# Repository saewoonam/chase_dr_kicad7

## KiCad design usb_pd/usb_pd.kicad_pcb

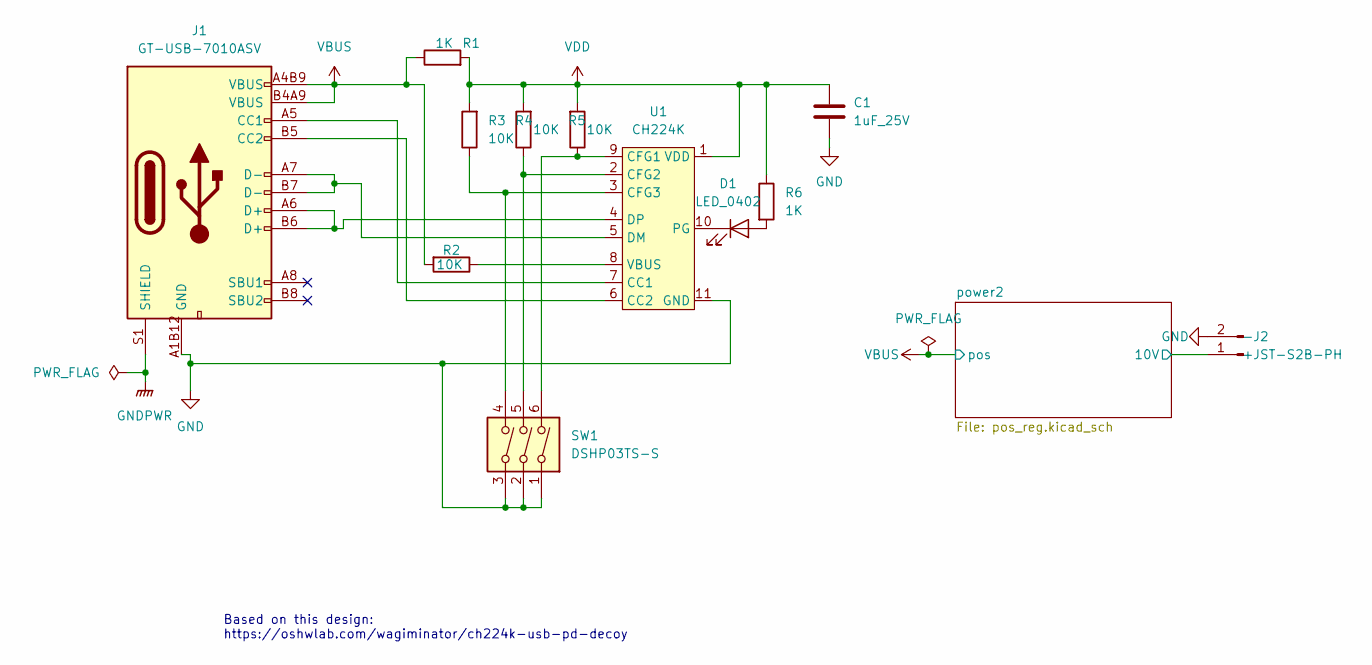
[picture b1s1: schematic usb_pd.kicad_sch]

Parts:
C1: 1uF_25V; C_0603_1608Metric_Pad1.08x0.95mm_HandSolder; MPN CL10A105KB8NNNC; LCSC C15849
D1: LED_0402; LED_0402_1005Metric; MPN BL-HGE37A-AV-TRB; LCSC C165979
J1: GT-USB-7010ASV; USB-C-GT-USB-7010ASV; LCSC C2988369
J2: JST-S2B-PH; JST_PH_S2B-PH-K_1x02_P2.00mm_Horizontal; MPN S2B-PH-K-S(LF)(SN); LCSC C173752
R1, R6: 1K; R_0603_1608Metric_Pad0.98x0.95mm_HandSolder; MPN 0603WAF1001T5E; LCSC C21190
R2, R3, R4, R5: 10K; R_0603_1608Metric_Pad0.98x0.95mm_HandSolder; MPN 0603WAF1002T5E; LCSC C25804
SW1: DSHP03TS-S; SW-SMD_DSHP03TS-S; LCSC C319051
U1: CH224K; ESSOP-10_L4.9-W3.9-P1.0-LS6.0-TL-EP; LCSC C970725

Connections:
/power2/10V: J2.1 (+); also elsewhere on the board
GNDPWR: J1.S1 (SHIELD), J1.S2 (SHIELD), J1.S3 (SHIELD), J1.S4 (SHIELD)
unnamed: D1.2 (A), R6.2
unnamed: D1.1 (K), U1.10 (PG)
unnamed: J1.A5 (CC1), U1.7 (CC1)
unnamed: J1.B5 (CC2), U1.6 (CC2)
unnamed: R5.1, SW1.6, U1.9 (CFG1)
unnamed: R4.1, SW1.5, U1.2 (CFG2)
unnamed: R3.1, SW1.4, U1.3 (CFG3)
unnamed: J1.A7 (D-), J1.B7 (D-), U1.5 (DM)
unnamed: J1.A6 (D+), J1.B6 (D+), U1.4 (DP)
unnamed: R2.1, U1.8 (VBUS)
VBUS: J1.A4B9 (VBUS), J1.B4A9 (VBUS), R1.1, R2.2; also elsewhere on the board
VDD: C1.1, R1.2, R3.2, R4.2, R5.2, R6.1, U1.1 (VDD)

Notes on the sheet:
Based on this design: https://oshwlab.com/wagiminator/ch224k-usb-pd-decoy

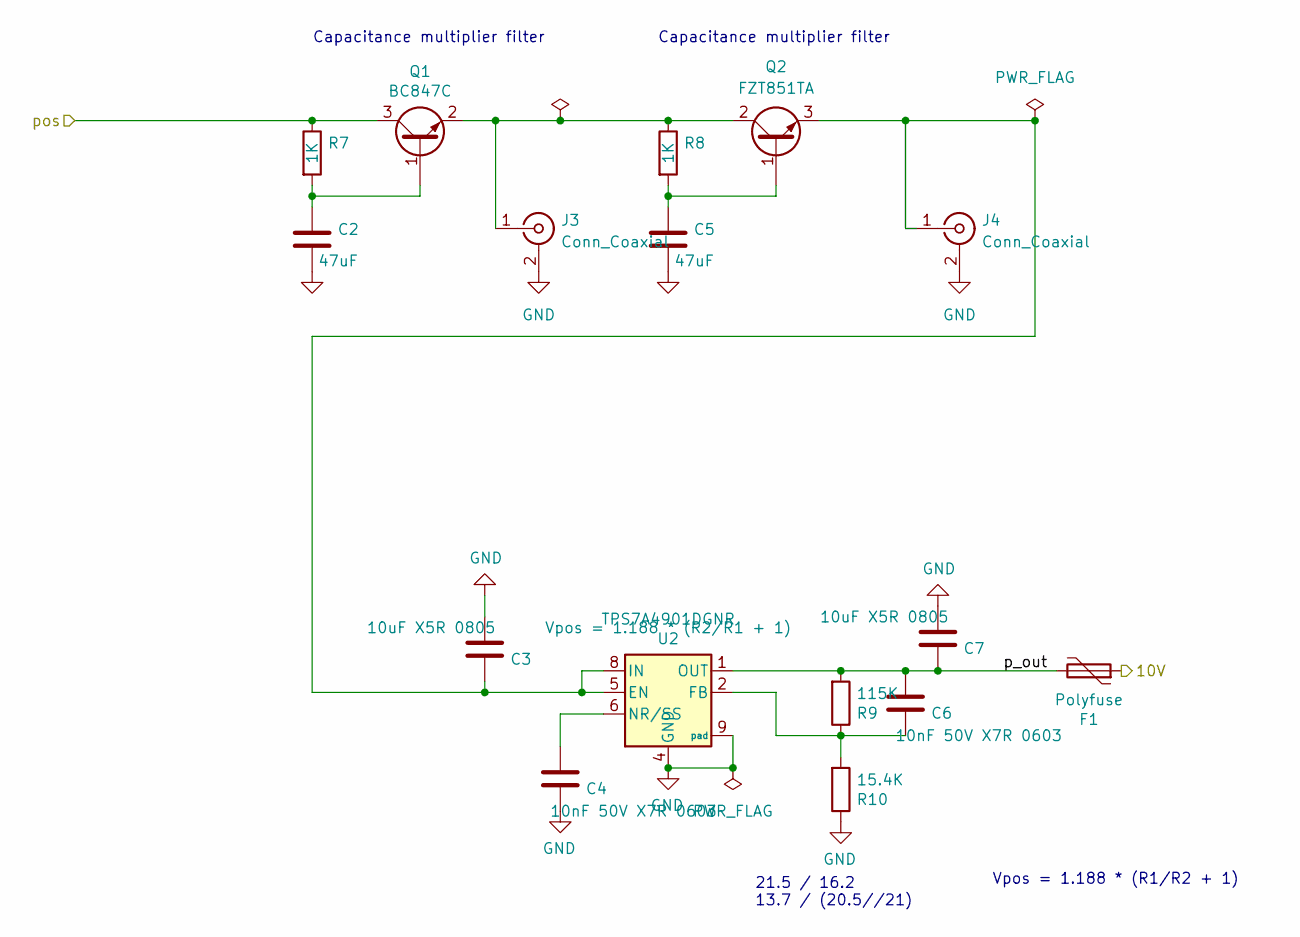
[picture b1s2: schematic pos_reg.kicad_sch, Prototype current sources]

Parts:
C2, C5: 47uF; C_1210_3225Metric_Pad1.33x2.70mm_HandSolder; MPN GRM32ER71A476KE15L; LCSC C84494
C3, C7: 10uF X5R 0805; C_0805_2012Metric_Pad1.18x1.45mm_HandSolder; MPN CL21A106KAYNNNE; LCSC C15850
C4, C6: 10nF 50V X7R 0603; C_0603_1608Metric_Pad1.08x0.95mm_HandSolder; MPN CL05B103KB5NNNC; LCSC C57112
F1: Polyfuse; Fuse_0603_1608Metric_Pad1.05x0.95mm_HandSolder; MPN TLC-FSMD020; LCSC C261935
J3, J4: Conn_Coaxial; U.FL_Hirose_U.FL-R-SMT-1_Vertical; LCSC C88374
Q1: BC847C; SOT-23; MPN BC847C,215; LCSC C8664
Q2: FZT851TA; SOT-223-3_TabPin2; MPN FZT851TA; LCSC C87950
R7, R8: 1K; R_0603_1608Metric_Pad0.98x0.95mm_HandSolder; MPN 0603WAF1001T5E; LCSC C21190
R9: 115K; R_0603_1608Metric_Pad0.98x0.95mm_HandSolder; MPN RC0603FR-07115KL; LCSC C137806
R10: 15.4K; R_0603_1608Metric_Pad0.98x0.95mm_HandSolder; LCSC C185370
U2: TPS7A4901DGNR; MSOP-8-1EP_3x3mm_P0.65mm_EP1.68x1.88mm; MPN TPS7A4901DGNR; LCSC C16430

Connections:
/power2/10V: F1.1; also elsewhere on the board
/power2/p_out: C6.2, C7.1, F1.2, R9.2, U2.1 (OUT)
unnamed: J3.1 (In), Q1.2 (E), Q2.2 (C), R8.1
unnamed: C3.1, J4.1 (In), Q2.3 (E), U2.5 (EN), U2.8 (IN)
unnamed: C2.1, Q1.1 (B), R7.2
unnamed: C5.1, Q2.1 (B), R8.2
unnamed: C6.1, R9.1, R10.2, U2.2 (FB)
unnamed: C4.2, U2.6 (NR/SS)
VBUS: Q1.3 (C), R7.1; also elsewhere on the board

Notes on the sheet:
Vpos = 1.188 * (R1/R2 + 1)
Capacitance multiplier filter
21.5 / 16.2 13.7 / (20.5//21)

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
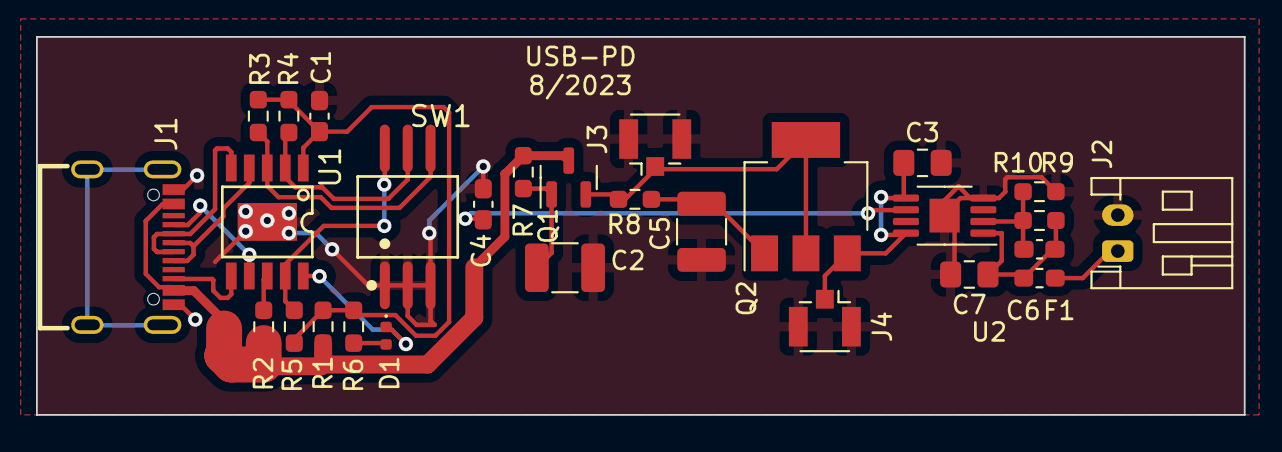
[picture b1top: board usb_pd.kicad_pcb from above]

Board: 2 copper layers, 67.1 x 21.0 mm, 28 parts (0 on the bottom side), 22 nets.

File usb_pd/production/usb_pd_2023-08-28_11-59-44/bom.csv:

Designator,Footprint,Quantity,Value,LCSC Part #
C1,0603,1,1uF_25V,C15849
"C2, C5",1210,2,47uF,C84494
"C3, C7",0805,2,10uF X5R 0805,C15850
"C4, C6",0603,2,10nF 50V X7R 0603,C57112
D1,0402,1,LED_0402,C165979
F1,0603,1,Polyfuse,C261935
J1,USB-C-GT-USB-7010ASV,1,GT-USB-7010ASV,C2988369
J2,JST_PH_S2B-PH-K_1x02_P2.00mm_Horizontal,1,JST-B2B-PH,C131337
"J3, J4",U.FL_Hirose_U.FL-R-SMT-1_Vertical,2,Conn_Coaxial,C88373
Q1,SOT-23,1,BC847C,C8664
Q2,SOT-223-3_TabPin2,1,FZT851TA,C87950
"R1, R6, R7, R8",0603,4,1K,C21190
R10,0603,1,15.4K,C185370
"R2, R3, R4, R5",0603,4,10K,C25804
R9,0603,1,115K,C137806
SW1,SW-SMD_DSHP03TS-S,1,DSHP03TS-S,C319051
U1,ESSOP-10_L4.9-W3.9-P1.0-LS6.0-TL-EP,1,CH224K,C970725
U2,MSOP-8-1EP_3x3mm_P0.65mm_EP1.68x1.88mm_ThermalVias,1,TPS7A4901DGNR,C16430

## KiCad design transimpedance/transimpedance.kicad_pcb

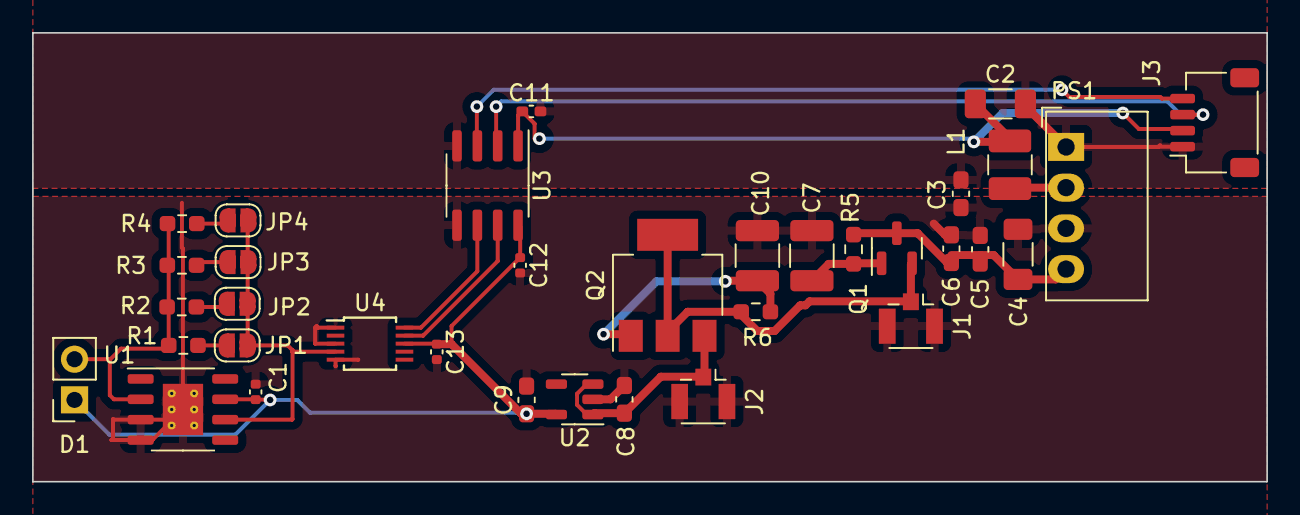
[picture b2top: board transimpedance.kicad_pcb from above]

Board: 2 copper layers, 77.0 x 28.0 mm, 35 parts (0 on the bottom side), 20 nets.

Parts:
C1, C12, C13: 100nF_0402; C_0402_1005Metric
C2: 4.7uF_1206_50V; C_1206_3216Metric_Pad1.33x1.80mm_HandSolder
C3: 1nF; C_0603_1608Metric_Pad1.08x0.95mm_HandSolder
C4: 10uF_1206_50V; C_1206_3216Metric_Pad1.33x1.80mm_HandSolder
C5: 100nF; C_0603_1608Metric_Pad1.08x0.95mm_HandSolder
C6: 10nF; C_0603_1608Metric_Pad1.08x0.95mm_HandSolder
C7, C10: 47uF; C_1210_3225Metric_Pad1.33x2.70mm_HandSolder
C8, C9: 1uF; C_0603_1608Metric_Pad1.08x0.95mm_HandSolder
C11: 100nF_0402; C_0402_1005Metric_Pad0.74x0.62mm_HandSolder
D1: D_Photo_Filled; PinSocket_1x02_P2.54mm_Vertical
J1, J2: Conn_Coaxial; U.FL_Hirose_U.FL-R-SMT-1_Vertical
J3: JST_SH_Conn_01x04_i2c_horizontal; JST_SH_SM04B-SRSS-TB_1x04-1MP_P1.00mm_Horizontal
JP1, JP2, JP3, JP4: Jumper_2_Open; SolderJumper-2_P1.3mm_Open_RoundedPad1.0x1.5mm
L1: 6.8uH; L_1210_3225Metric_Pad1.42x2.65mm_HandSolder
PS1: B0305S; Converter_DCDC_Murata_MEE1SxxxxSC_THT
Q1: BC847C; SOT-23
Q2: FZT851TA; SOT-223-3_TabPin2
R1, R2: 100K; R_0603_1608Metric_Pad0.98x0.95mm_HandSolder
R3, R4: 10K; R_0603_1608Metric_Pad0.98x0.95mm_HandSolder
R5, R6: 1K; R_0603_1608Metric_Pad0.98x0.95mm_HandSolder
U1: OPA828IDR; SOIC-8-1EP_3.9x4.9mm_P1.27mm_EP2.514x3.2mm_ThermalVias
U2: LP5907MFX-3.3; SOT-23-5
U3: ISO1541; SOIC-8_3.9x4.9mm_P1.27mm
U4: ADS1115IDGS; TSSOP-10_3x3mm_P0.5mm

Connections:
+3.3V: C1.1, C9.1, C12.1, C13.1, D1.1 (K), U1.7 (V+), U2.5 (OUT), U3.8 (VCC2), U4.8 (VDD)
/uart_power/gnd_in: C2.2, C3.1, C11.2, J3.1 (gnd), PS1.1 (-Vin), U3.4 (GND1)
/uart_power/power_in: C2.1, C11.1, J3.2 (VCC), L1.2, U3.1 (VCC1)
GND: C1.2, C3.2, C4.2, C5.1, C6.1, C7.2, C8.2, C9.2, C10.2, C12.2, C13.2, J1.2 (Ext), J2.2 (Ext), PS1.3 (0V), U1.3 (+), U1.4 (V-), U1.9 (EP), U2.2 (GND), U3.5 (GND2), U4.1 (ADDR), U4.3 (GND), U4.5 (AIN1)
unnamed: D1.2 (A), R1.1, R2.1, R3.1, R4.1, U1.2 (-)
unnamed: J1.1 (In), Q1.2 (E), Q2.2 (C), R6.1
unnamed: C8.1, J2.1 (In), Q2.3 (E), U2.1 (IN), U2.3 (EN)
unnamed: J3.4 (SCL), U3.3 (SCL1)
unnamed: J3.3 (SDA), U3.2 (SDA1)
unnamed: JP1.1 (A), R1.2
unnamed: JP1.2 (B), JP2.2 (B), JP3.2 (B), JP4.2 (B), U1.6, U4.4 (AIN0)
unnamed: JP2.1 (A), R2.2
unnamed: JP3.1 (A), R3.2
unnamed: JP4.1 (A), R4.2
unnamed: L1.1, PS1.2 (+Vin)
unnamed: C4.1, C5.2, C6.2, PS1.4 (+Vout), Q1.3 (C), R5.1
unnamed: C7.1, Q1.1 (B), R5.2
unnamed: C10.1, Q2.1 (B), R6.2
unnamed: U3.6 (SCL2), U4.10 (SCL)
unnamed: U3.7 (SDA2), U4.9 (SDA)

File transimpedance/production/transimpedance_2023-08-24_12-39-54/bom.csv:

Designator,Footprint,Quantity,Value,LCSC Part #
"C1, C12, C13",0402,3,100nF_0402,C14663
"C10, C7",1210,2,47uF,C84494
C11,0402,1,100nF_0402,C56392
C2,1206,1,4.7uF_1206_50V,C29823
C3,0603,1,1nF,C100040
C4,1206,1,10uF_1206_50V,C13585
C5,0603,1,100nF,C14663
C6,0603,1,10nF,C57112
"C8, C9",0603,2,1uF,C15849
D1,PinSocket_1x02_P2.54mm_Vertical,1,D_Photo_Filled,
"J1, J2",U.FL_Hirose_U.FL-R-SMT-1_Vertical,2,Conn_Coaxial,C88373
J3,JST_SH_BM04B-SRSS-TB_1x04-1MP_P1.00mm_Vertical,1,JST_SH_Conn_01x04_i2c_horizontal,C371571
"JP1, JP2, JP3, JP4",SolderJumper-2_P1.3mm_Open_RoundedPad1.0x1.5mm,4,Jumper_2_Open,
L1,1210,1,6.8uH,C87558
PS1,Converter_DCDC_Murata_MEE1SxxxxSC_THT,1,B0305S,C909802
Q1,SOT-23,1,BC847C,C8664
Q2,SOT-223-3_TabPin2,1,FZT851TA,C87950
"R1, R2",0603,2,100K,C22936
"R3, R4",0603,2,10K,C25804
"R5, R6",0603,2,1K,C21190
U1,SOIC-8-1EP_3.9x4.9mm_P1.27mm_EP2.514x3.2mm_ThermalVias,1,OPA828IDR,C1850247
U2,SOT-23-5,1,LP5907MFX-3.3,C80670
U3,SOIC-8_3.9x4.9mm_P1.27mm,1,ISO1541,C143028
U4,TSSOP-10_3x3mm_P0.5mm,1,ADS1115IDGS,C37593

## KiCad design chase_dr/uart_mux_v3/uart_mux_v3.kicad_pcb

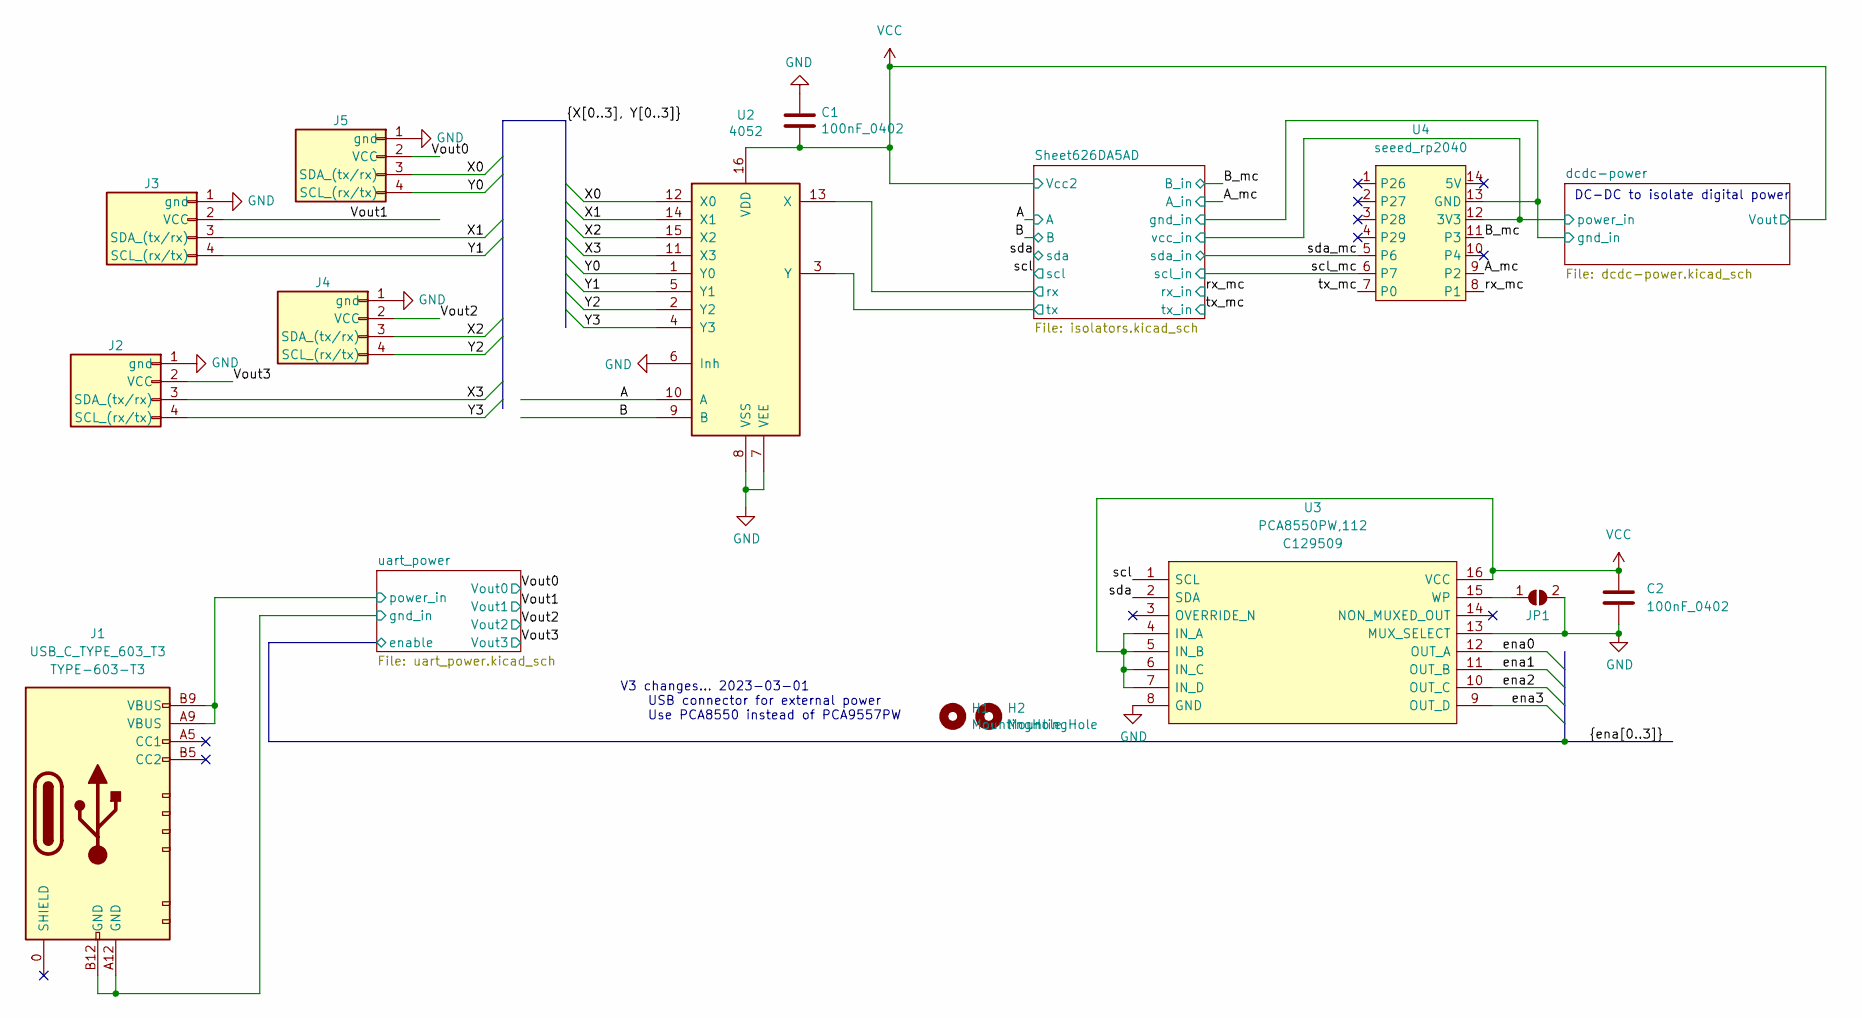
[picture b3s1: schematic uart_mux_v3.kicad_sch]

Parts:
C1, C2: 100nF_0402; C_0402_1005Metric_Pad0.74x0.62mm_HandSolder; MPN 0402B104K250NT; LCSC C56392
H1, H2: MountingHole; MountingHole_2.7mm_M2.5_Pad
J1: USB_C_TYPE_603_T3; USB-C-SMD_TYPE-603-T3; MPN TYPE-603-T3; LCSC C2689837
J2, J3, J4, J5: JST_SH_Conn_01x04_i2c_uart_horizontal; JST_SH_SM04B-SRSS-TB_1x04-1MP_P1.00mm_Horizontal; MPN A1001WR-S; LCSC C371571
JP1: SolderJumper_2_Open; SolderJumper-2_P1.3mm_Open_RoundedPad1.0x1.5mm
U2: 4052; TSSOP-16_4.4x5mm_P0.65mm; MPN SN74LV4052APWR; LCSC C8142
U3: PCA8550PW,112; TSSOP-16_4.4x5mm_P0.65mm; MPN PCA8550PW,112; LCSC C129509
U4: seeed_rp2040; DIP-XIAO-QTPY

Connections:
/A: U2.10 (A); also elsewhere on the board
/A_mc: U4.9 (P2); also elsewhere on the board
/B: U2.9 (B); also elsewhere on the board
/B_mc: U4.11 (P3); also elsewhere on the board
/Sheet626DA5AD/rx: U2.13 (X); also elsewhere on the board
/Sheet626DA5AD/tx: U2.3 (Y); also elsewhere on the board
/Vout0: J5.2 (VCC); also elsewhere on the board
/Vout1: J3.2 (VCC); also elsewhere on the board
/Vout2: J4.2 (VCC); also elsewhere on the board
/Vout3: J2.2 (VCC); also elsewhere on the board
/X0: J5.3 (SDA_(tx/rx)), U2.12 (X0)
/X1: J3.3 (SDA_(tx/rx)), U2.14 (X1)
/X2: J4.3 (SDA_(tx/rx)), U2.15 (X2)
/X3: J2.3 (SDA_(tx/rx)), U2.11 (X3)
/Y0: J5.4 (SCL_(rx/tx)), U2.1 (Y0)
/Y1: J3.4 (SCL_(rx/tx)), U2.5 (Y1)
/Y2: J4.4 (SCL_(rx/tx)), U2.2 (Y2)
/Y3: J2.4 (SCL_(rx/tx)), U2.4 (Y3)
/ena0: U3.12 (OUT_A); also elsewhere on the board
/ena1: U3.11 (OUT_B); also elsewhere on the board
/ena2: U3.10 (OUT_C); also elsewhere on the board
/ena3: U3.9 (OUT_D); also elsewhere on the board
/rx_mc: U4.8 (P1); also elsewhere on the board
/scl: U3.1 (SCL); also elsewhere on the board
/scl_mc: U4.6 (P7); also elsewhere on the board
/sda: U3.2 (SDA); also elsewhere on the board
/sda_mc: U4.5 (P6); also elsewhere on the board
/tx_mc: U4.7 (P0); also elsewhere on the board
/uart_power/gnd_in: J1.A12 (GND), J1.B12 (GND); also elsewhere on the board
/uart_power/power_in: J1.A9 (VBUS), J1.B9 (VBUS); also elsewhere on the board
GNDPWR: U4.13 (GND); also elsewhere on the board
unnamed: JP1.1 (A), U3.15 (WP)
VCC: C1.2, C2.1, U2.16 (VDD), U3.4 (IN_A), U3.5 (IN_B), U3.6 (IN_C), U3.7 (IN_D), U3.16 (VCC); also elsewhere on the board
VD: U4.12 (3V3); also elsewhere on the board

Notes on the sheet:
V3 changes... 2023-03-01 USB connector for external power Use PCA8550 instead of PCA9557PW
DC-DC to isolate digital power

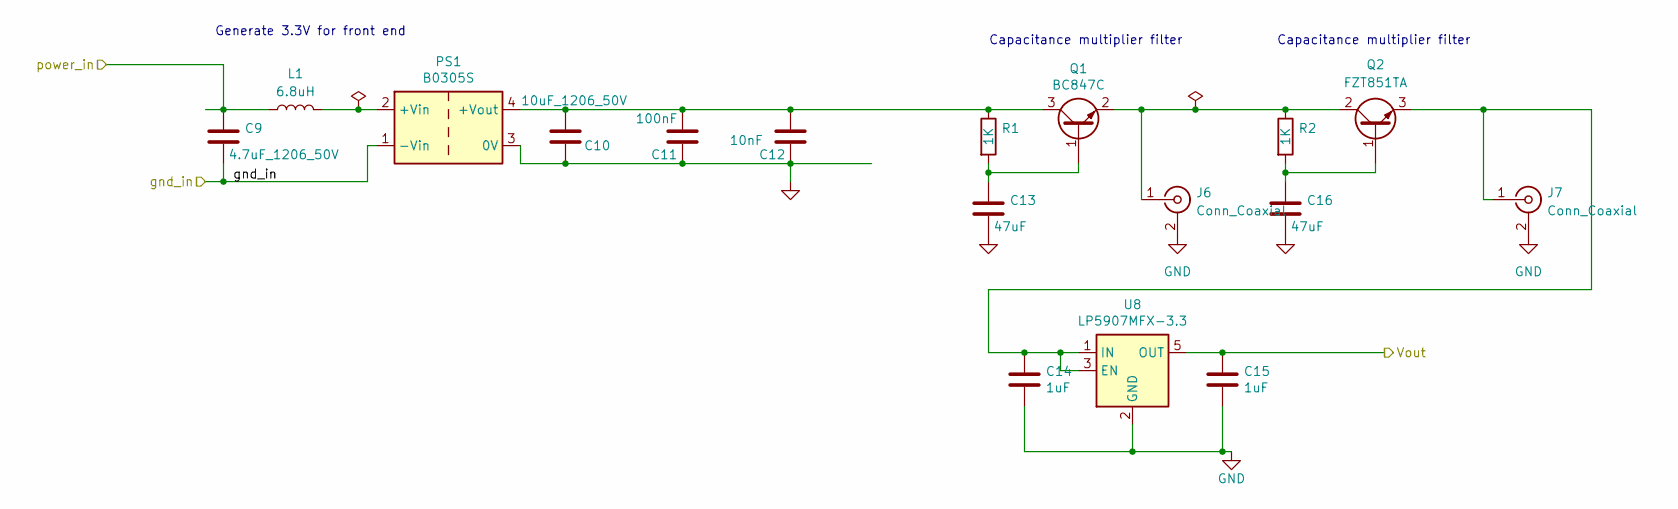
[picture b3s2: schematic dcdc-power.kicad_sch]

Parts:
C9: 4.7uF_1206_50V; C_1206_3216Metric_Pad1.33x1.80mm_HandSolder; MPN 1206B475K500NT; LCSC C29823
C10: 10uF_1206_50V; C_1206_3216Metric_Pad1.33x1.80mm_HandSolder; MPN CL31A106KBHNNNE; LCSC C13585
C11: 100nF; C_0603_1608Metric_Pad1.08x0.95mm_HandSolder; MPN CC0603KRX7R9BB104; LCSC C14663
C12: 10nF; C_0603_1608Metric_Pad1.08x0.95mm_HandSolder; MPN 0603B103K500NT; LCSC C57112
C13, C16: 47uF; C_1210_3225Metric_Pad1.33x2.70mm_HandSolder; MPN GRM32ER71A476KE15L; LCSC C84494
C14, C15: 1uF; C_0603_1608Metric_Pad1.08x0.95mm_HandSolder; MPN CL10A105KB8NNNC; LCSC C15849
J6, J7: Conn_Coaxial; U.FL_Hirose_U.FL-R-SMT-1_Vertical; LCSC C88373
L1: 6.8uH; L_1210_3225Metric_Pad1.42x2.65mm_HandSolder; MPN NLCV32T-6R8M-PFR; LCSC C87558
PS1: B0305S; Converter_DCDC_Murata_MEE1SxxxxSC_THT; MPN B0305S; LCSC C909802
Q1: BC847C; SOT-23; MPN BC847C,215; LCSC C8664
Q2: FZT851TA; SOT-223-3_TabPin2; MPN FZT851TA; LCSC C87950
R1, R2: 1K; R_0603_1608Metric_Pad0.98x0.95mm_HandSolder; MPN 0603WAF1001T5E; LCSC C21190
U8: LP5907MFX-3.3; SOT-23-5; MPN LP5907MFX-3.3/NOPB; LCSC C80670

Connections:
GNDPWR: C9.2, PS1.1 (-Vin); also elsewhere on the board
unnamed: J6.1 (In), Q1.2 (E), Q2.2 (C), R2.1
unnamed: C14.1, J7.1 (In), Q2.3 (E), U8.1 (IN), U8.3 (EN)
unnamed: L1.1, PS1.2 (+Vin)
unnamed: C10.1, C11.2, C12.2, PS1.4 (+Vout), Q1.3 (C), R1.1
unnamed: C13.1, Q1.1 (B), R1.2
unnamed: C16.1, Q2.1 (B), R2.2
VCC: C15.1, U8.5 (OUT); also elsewhere on the board
VD: C9.1, L1.2; also elsewhere on the board

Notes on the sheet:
Generate 3.3V for front end
Capacitance multiplier filter

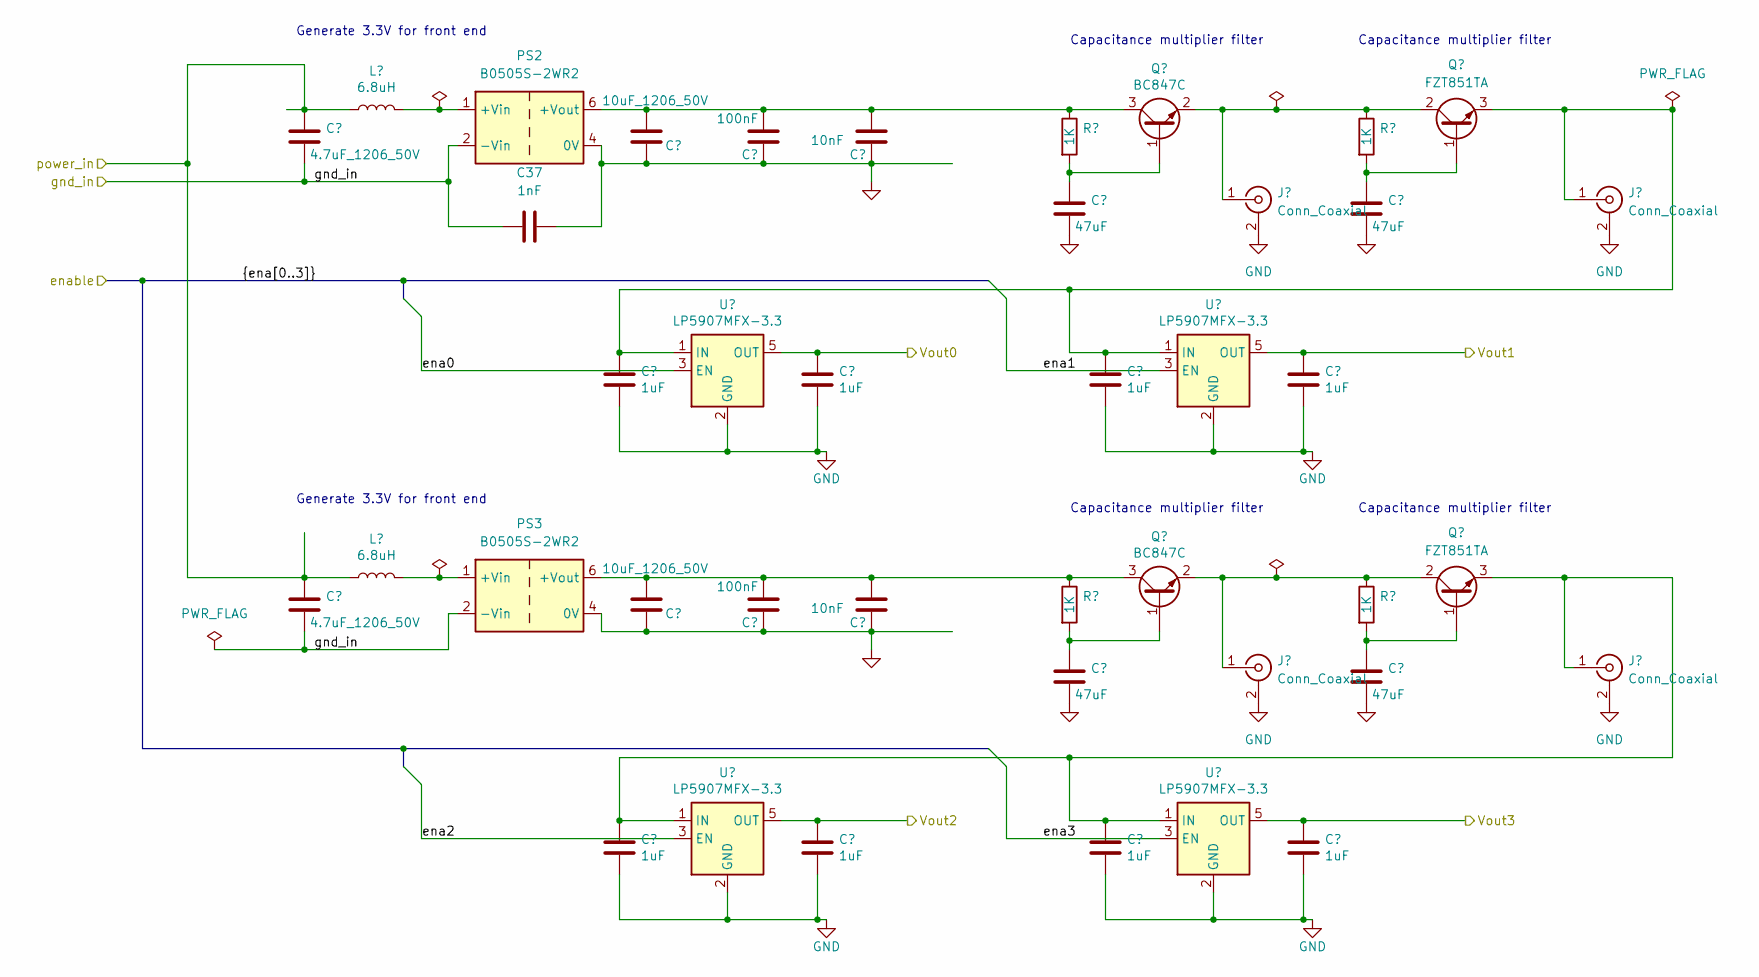
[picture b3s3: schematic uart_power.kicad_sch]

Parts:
C17, C18: 4.7uF_1206_50V; C_1206_3216Metric_Pad1.33x1.80mm_HandSolder; MPN 1206B475K500NT; LCSC C29823
C19, C20, C25, C26, C31, C32, C33, C34: 1uF; C_0603_1608Metric_Pad1.08x0.95mm_HandSolder; MPN CL10A105KB8NNNC; LCSC C15849
C21, C22: 10uF_1206_50V; C_1206_3216Metric_Pad1.33x1.80mm_HandSolder; MPN CL31A106KBHNNNE; LCSC C13585
C23, C24: 100nF; C_0603_1608Metric_Pad1.08x0.95mm_HandSolder; MPN CC0603KRX7R9BB104; LCSC C14663
C27, C28: 10nF; C_0603_1608Metric_Pad1.08x0.95mm_HandSolder; MPN 0603B103K500NT; LCSC C57112
C29, C30, C35, C36: 47uF; C_1210_3225Metric_Pad1.33x2.70mm_HandSolder; MPN GRM32ER71A476KE15L; LCSC C84494
C37: 1nF; C_0603_1608Metric_Pad1.08x0.95mm_HandSolder; MPN CC0603KRX7R9BB102; LCSC C100040
J8, J9, J10, J11: Conn_Coaxial; U.FL_Hirose_U.FL-R-SMT-1_Vertical; LCSC C88373
L2, L3: 6.8uH; L_1210_3225Metric_Pad1.42x2.65mm_HandSolder; MPN NLCV32T-6R8M-PFR; LCSC C87558
PS2, PS3: B0505S-2WR2; PWRM-TH_B0505S-2WR2_C2992385; MPN B0505S-2WR2; LCSC C2992385
Q3, Q4: BC847C; SOT-23; MPN BC847C,215; LCSC C8664
Q5, Q6: FZT851TA; SOT-223-3_TabPin2; MPN FZT851TA; LCSC C87950
R3, R4, R5, R6: 1K; R_0603_1608Metric_Pad0.98x0.95mm_HandSolder; MPN 0603WAF1001T5E; LCSC C21190
U9, U10, U11, U12: LP5907MFX-3.3; SOT-23-5; MPN LP5907MFX-3.3/NOPB; LCSC C80670

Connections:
/Vout0: C25.1, U9.5 (OUT); also elsewhere on the board
/Vout1: C33.1, U11.5 (OUT); also elsewhere on the board
/Vout2: C26.1, U10.5 (OUT); also elsewhere on the board
/Vout3: C34.1, U12.5 (OUT); also elsewhere on the board
/ena0: U9.3 (EN); also elsewhere on the board
/ena1: U11.3 (EN); also elsewhere on the board
/ena2: U10.3 (EN); also elsewhere on the board
/ena3: U12.3 (EN); also elsewhere on the board
/uart_power/gnd_in: C17.2, C18.2, C37.1, PS2.2 (-Vin), PS3.2 (-Vin); also elsewhere on the board
/uart_power/power_in: C17.1, C18.1, L2.2, L3.2; also elsewhere on the board
unnamed: J8.1 (In), Q3.2 (E), Q5.2 (C), R5.1
unnamed: J9.1 (In), Q4.2 (E), Q6.2 (C), R6.1
unnamed: C19.1, C31.1, J10.1 (In), Q5.3 (E), U9.1 (IN), U11.1 (IN)
unnamed: C20.1, C32.1, J11.1 (In), Q6.3 (E), U10.1 (IN), U12.1 (IN)
unnamed: L2.1, PS2.1 (+Vin)
unnamed: C21.1, C23.2, C27.2, PS2.6 (+Vout), Q3.3 (C), R3.1
unnamed: L3.1, PS3.1 (+Vin)
unnamed: C22.1, C24.2, C28.2, PS3.6 (+Vout), Q4.3 (C), R4.1
unnamed: C29.1, Q3.1 (B), R3.2
unnamed: C30.1, Q4.1 (B), R4.2
unnamed: C35.1, Q5.1 (B), R5.2
unnamed: C36.1, Q6.1 (B), R6.2

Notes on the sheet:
Generate 3.3V for front end
Capacitance multiplier filter

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
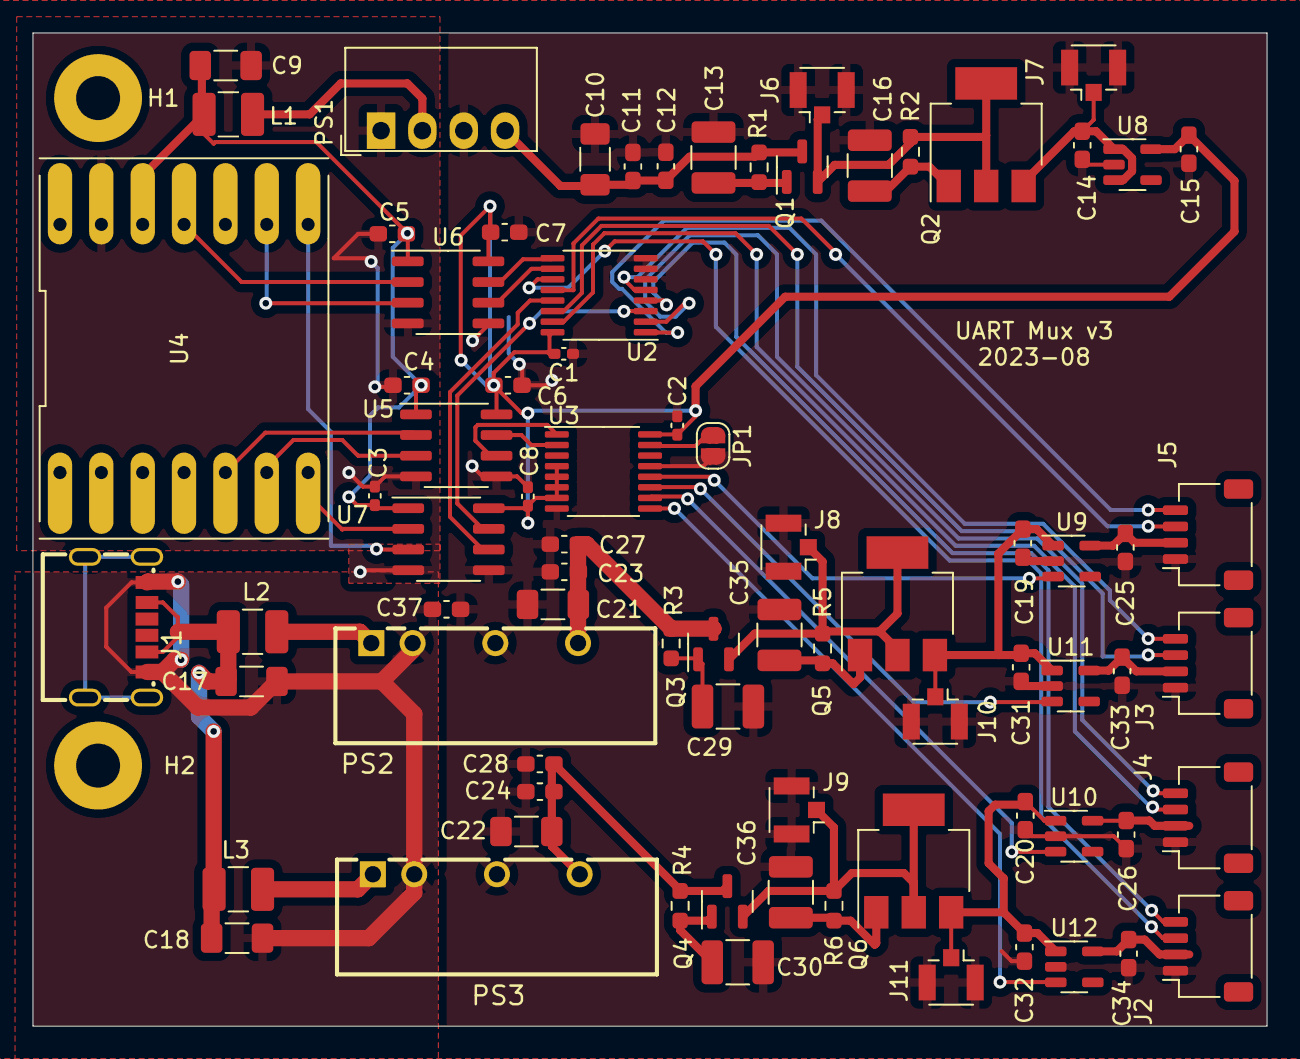
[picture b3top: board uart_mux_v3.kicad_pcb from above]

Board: 2 copper layers, 75.8 x 61.0 mm, 80 parts (0 on the bottom side), 53 nets.

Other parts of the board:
C3, C8: 100nF_0402; C_0402_1005Metric_Pad0.74x0.62mm_HandSolder
C4, C5, C6, C7: 100nF; C_0603_1608Metric_Pad1.08x0.95mm_HandSolder
U5: ISO1541; SOIC-8_3.9x4.9mm_P1.27mm
U6: PI120; SOIC-8_3.9x4.9mm_P1.27mm
U7: PI121; SOIC-8_3.9x4.9mm_P1.27mm

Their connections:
/A: U6.6 (VOB); also elsewhere on the board
/A_mc: U6.3 (VIB); also elsewhere on the board
/B: U6.7 (VOA); also elsewhere on the board
/B_mc: U6.2 (VIA); also elsewhere on the board
/Sheet626DA5AD/rx: U7.6 (VIB); also elsewhere on the board
/Sheet626DA5AD/tx: U7.7 (VOA); also elsewhere on the board
/rx_mc: U7.3 (VOB); also elsewhere on the board
/scl: U5.6 (SCL2); also elsewhere on the board
/scl_mc: U5.3 (SCL1); also elsewhere on the board
/sda: U5.7 (SDA2); also elsewhere on the board
/sda_mc: U5.2 (SDA1); also elsewhere on the board
/tx_mc: U7.2 (VIA); also elsewhere on the board
GNDPWR: C3.2, C4.2, C5.2, U5.4 (GND1), U6.4 (GND1), U7.4 (GND1); also elsewhere on the board
VCC: C6.2, C7.2, C8.1, U5.8 (VCC2), U6.8 (VDD2), U7.8 (VDD2); also elsewhere on the board
VD: C3.1, C4.1, C5.1, U5.1 (VCC1), U6.1 (VDD1), U7.1 (VDD1); also elsewhere on the board

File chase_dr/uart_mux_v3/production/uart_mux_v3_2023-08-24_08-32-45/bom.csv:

Designator,Footprint,Quantity,Value,LCSC Part #
"C1, C2, C3, C8",0402,4,100nF_0402,C56392
"C10, C21, C22",1206,3,10uF_1206_50V,C13585
"C11, C23, C24, C4, C5, C6, C7",0603,7,100nF,C14663
"C12, C27, C28",0603,3,10nF,C57112
"C13, C16, C29, C30, C35, C36",1210,6,47uF,C84494
"C14, C15, C19, C20, C25, C26, C31, C32, C33, C34",0603,10,1uF,C15849
"C17, C18, C9",1206,3,4.7uF_1206_50V,C29823
C37,0603,1,1nF,C100040
J1,USB-C-SMD_TYPE-603-T3,1,USB_C_TYPE_603_T3,C2689837
"J10, J11, J6, J7, J8, J9",U.FL_Hirose_U.FL-R-SMT-1_Vertical,6,Conn_Coaxial,C88373
"J2, J3, J4, J5",JST_SH_SM04B-SRSS-TB_1x04-1MP_P1.00mm_Horizontal,4,JST_SH_Conn_01x04_i2c_uart_horizontal,C371571
JP1,SolderJumper-2_P1.3mm_Open_RoundedPad1.0x1.5mm,1,SolderJumper_2_Open,
"L1, L2, L3",1210,3,6.8uH,C87558
PS1,Converter_DCDC_Murata_MEE1SxxxxSC_THT,1,B0305S,C909802
"PS2, PS3",PWRM-TH_B0505S-2WR2_C2992385,2,B0505S-2WR2,C2992385
"Q1, Q3, Q4",SOT-23,3,BC847C,C8664
"Q2, Q5, Q6",SOT-223-3_TabPin2,3,FZT851TA,C87950
"R1, R2, R3, R4, R5, R6",0603,6,1K,C21190
"U10, U11, U12, U8, U9",SOT-23-5,5,LP5907MFX-3.3,C80670
U2,TSSOP-16_4.4x5mm_P0.65mm,1,4052,C8142
U3,TSSOP-16_4.4x5mm_P0.65mm,1,"PCA8550PW,112",C129509
U5,SOIC-8_3.9x4.9mm_P1.27mm,1,ISO1541,C143028
U6,SOIC-8_3.9x4.9mm_P1.27mm,1,PI120,C471591
U7,SOIC-8_3.9x4.9mm_P1.27mm,1,PI121,C471589
